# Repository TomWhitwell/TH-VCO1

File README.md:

# TH-VCO1

This is a Eurorack Layout for the [Thomas Henry VCO 1](http://www.birthofasynth.com/Thomas_Henry/Pages/VCO-1.html) Oscillator. 

**NB: All rights to this design rest with Thomas Henry. I do not claim or grant any copyright or license to this design. I am not selling any boards. I have not been able to contact Thomas, and will take this page down if he asks me to.** 

I made very minor changes from Thomas' original to make it work on 12v - detailed here: https://muffwiggler.com/forum/viewtopic.php?t=49671

This layout is for a modern LM13700 OTA replacing the old 3080, with a That 340 chip providing the matched transistor pairs. The only other non-standard components are a [2K 3300ppm Tempco](https://www.thonk.co.uk/shop/tempco-resistor-anakeohm-1-3300ppm-x3/) as R2, and a Polystyrene 1nf cap as C3.  

It all works very well, fantastic FM, nice looking and sounding sines. I was able to trim it to 4-5 octaves before getting bored. I haven't used multi-turn trimmers, so it might be harder to trim more accurately. On my second build I haven't trimmed anything, and it works beautifully for my needs. 

Quick demo here: https://www.instagram.com/p/_etQT6DmdM/

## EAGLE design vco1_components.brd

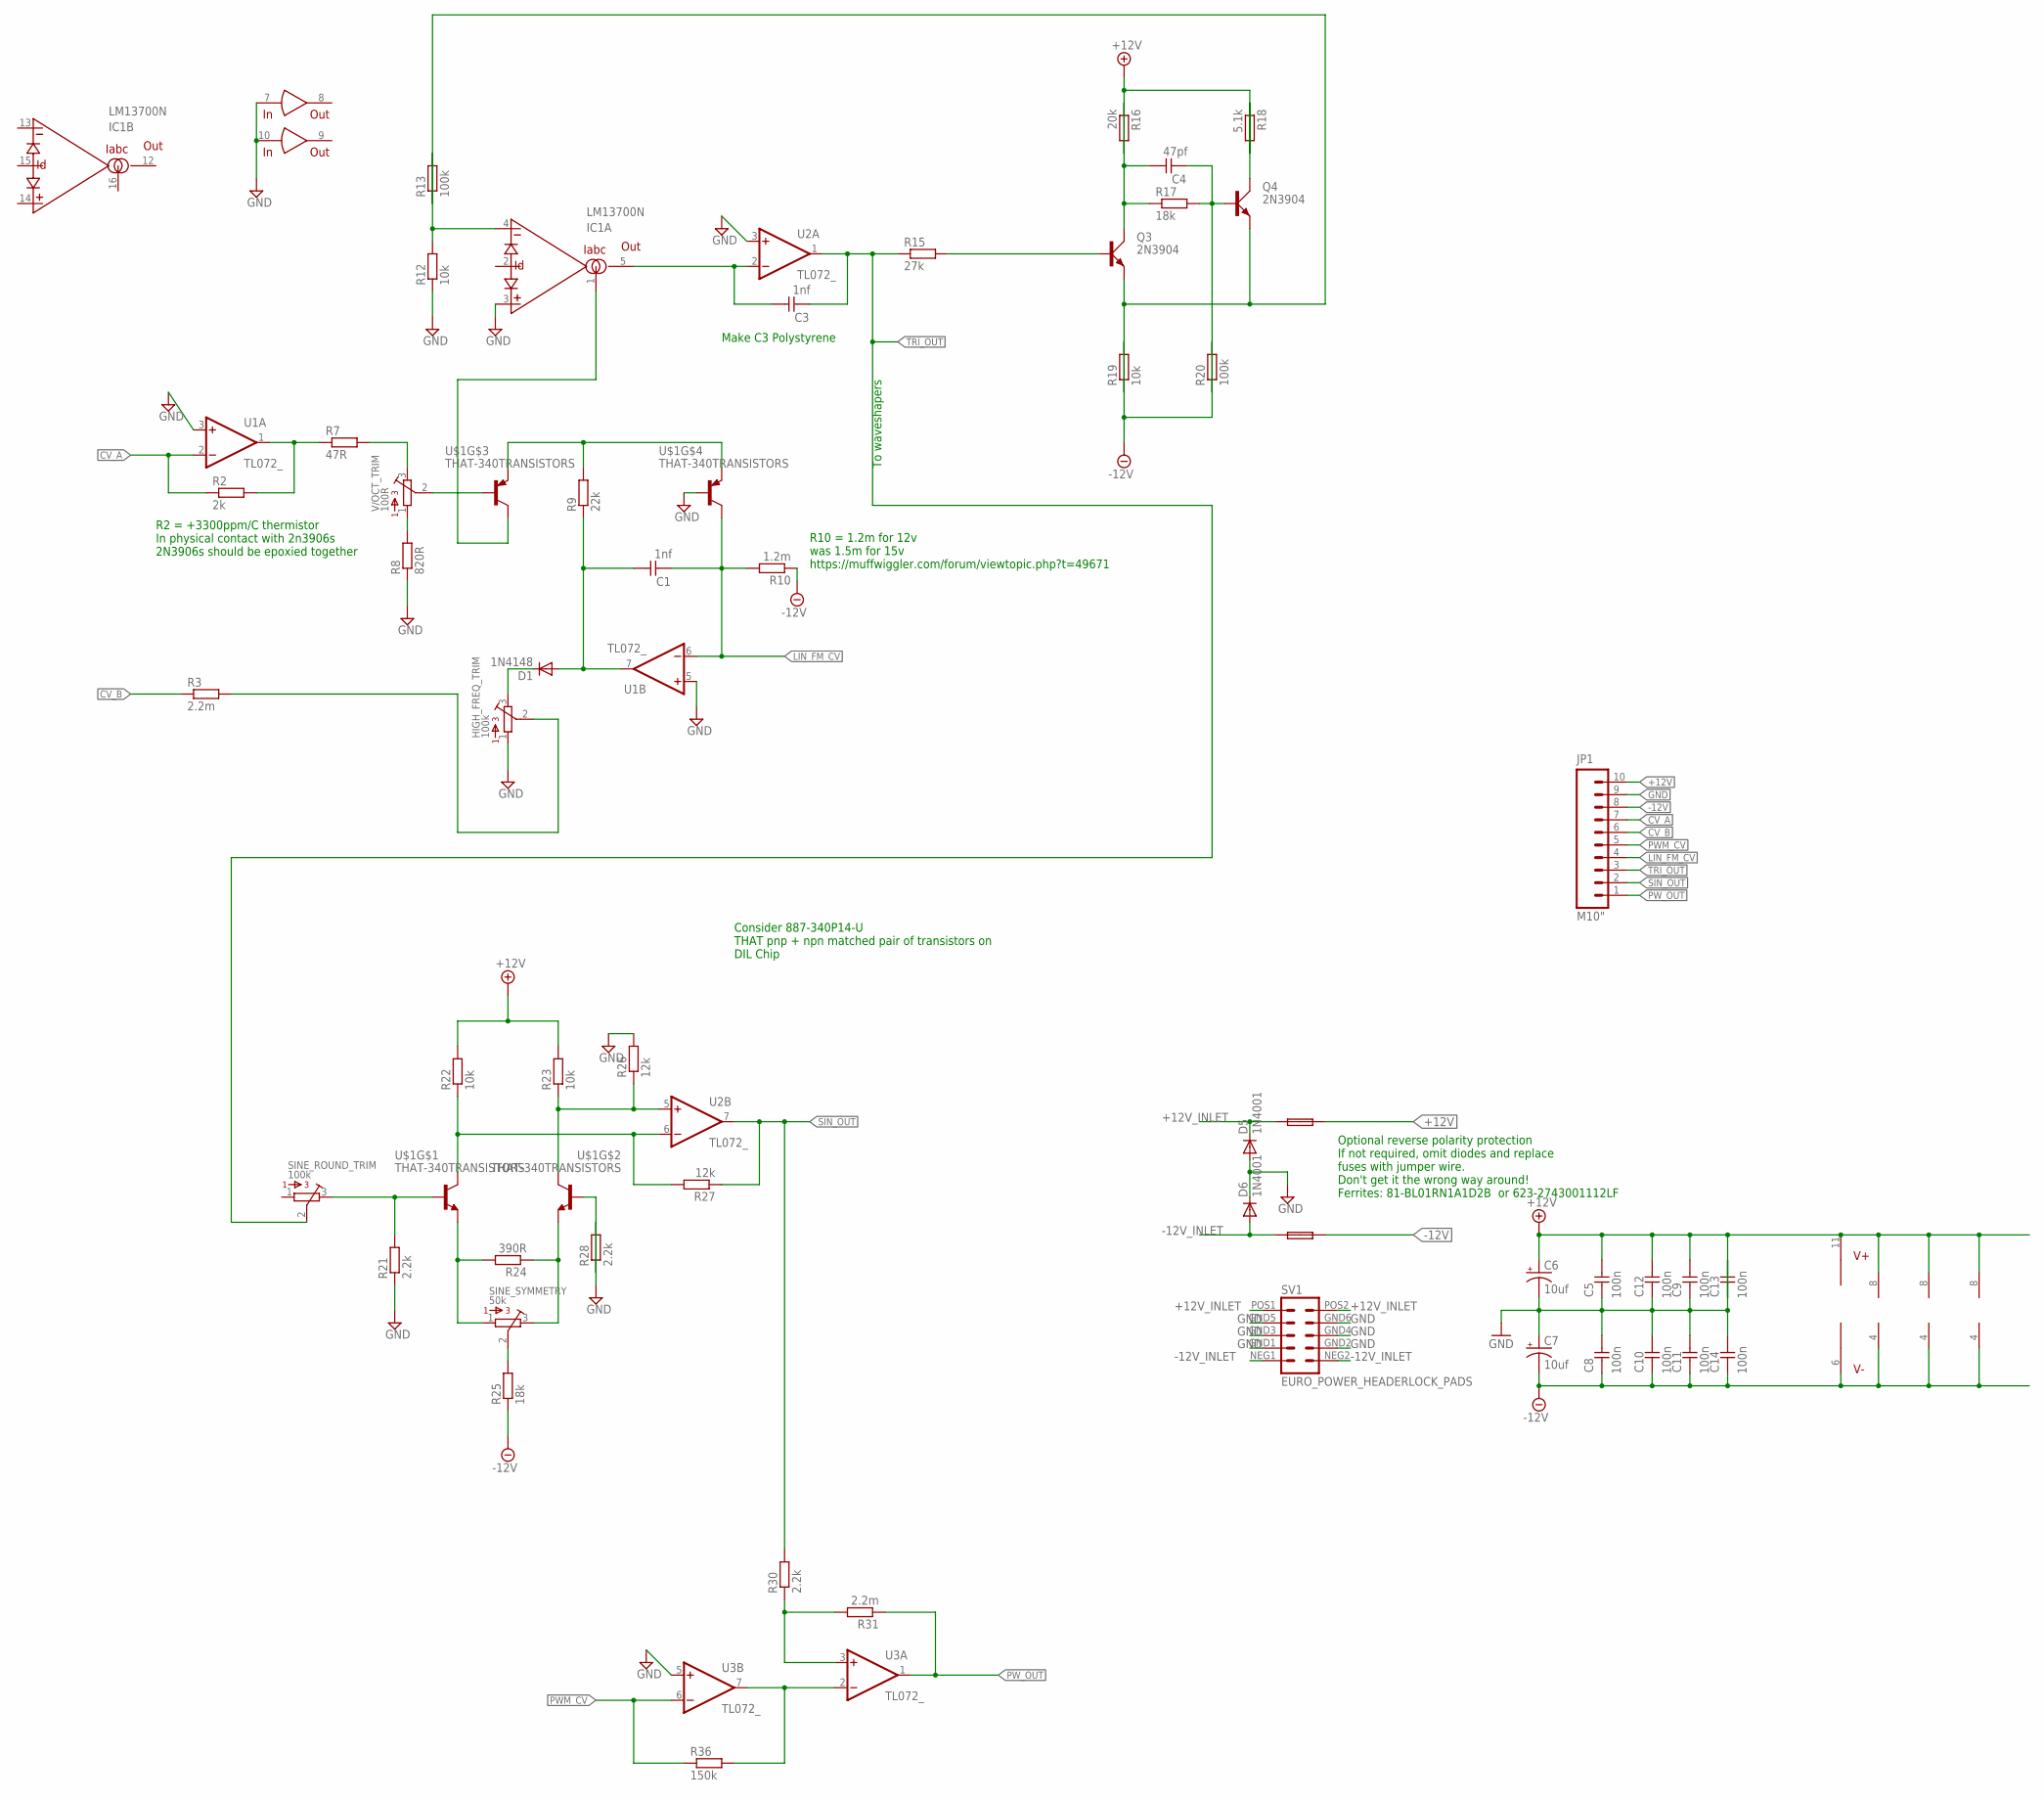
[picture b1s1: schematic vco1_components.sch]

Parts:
C1, C3: 1nf; C050-024X044
C4: 47pf; C050-024X044
C5, C8, C9, C10, C11, C12, C13, C14: 100n; C050-024X044
C6, C7: 10uf; CPOL-RADIAL-10UF-25V
D1: 1N4148; DO35-7
D5, D6: 1N4001; DO41-10
F1, F2: FUSE; C050H075X075
HIGH_FREQ_TRIM: 100k; BOURNS_3362P_TRIMMER
IC1: LM13700N; DIL16
JP1: M10"; 1X10
Q3, Q4: 2N3904; TO92D
R2: 2k; 7MM_RESISTOR
R3, R31: 2.2m; 7MM_RESISTOR
R7: 47R; 7MM_RESISTOR
R8: 820R; 7MM_RESISTOR
R9: 22k; 7MM_RESISTOR
R10: 1.2m; 7MM_RESISTOR
R12, R19, R22, R23: 10k; 7MM_RESISTOR
R13, R20: 100k; 7MM_RESISTOR
R15: 27k; 7MM_RESISTOR
R16: 20k; 7MM_RESISTOR
R17, R25: 18k; 7MM_RESISTOR
R18: 5.1k; 7MM_RESISTOR
R21, R28, R30: 2.2k; 7MM_RESISTOR
R24: 390R; 7MM_RESISTOR
R26, R27: 12k; 7MM_RESISTOR
R36: 150k; 7MM_RESISTOR
SINE_ROUND_TRIM: 100k; BOURNS_3362P_TRIMMER
SINE_SYMMETRY: 50k; BOURNS_3362P_TRIMMER
SV1: EURO_POWER_HEADERLOCK_PADS; EURO_PWR_HEADER_LOCK
U1, U2, U3: TL072_; DIL08
U$1: THAT-340TRANSISTORS; THAT340
V/OCT_TRIM: 100R; BOURNS_3362P_TRIMMER

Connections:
+12V: C5.1, C6.1 (+), C9.1, C12.1, C13.2, F1.2, IC1.11 (V+), JP1.10, R16.2, R18.2, R22.2, R23.2, U1.8 (V+), U2.8 (V+), U3.8 (V+)
+12V_INLET: D5.C, F1.1, SV1.POS1 (10), SV1.POS2 (9)
-12V: C7.2 (-), C8.2, C10.2, C11.2, C14.2, F2.2, IC1.6 (V-), JP1.8, R10.1, R19.2, R20.2, R25.1, U1.4 (V-), U2.4 (V-), U3.4 (V-)
-12V_INLET: D6.A, F2.1, SV1.NEG1 (2), SV1.NEG2 (1)
CV_A: JP1.7, R2.1, U1.2 (-IN)
CV_B: JP1.6, R3.1
GND: C5.2, C6.2 (-), C7.1 (+), C8.1, C9.2, C10.1, C11.1, C12.2, C13.1, C14.1, D5.A, D6.C, HIGH_FREQ_TRIM.1, IC1.3 (+IN), IC1.7 (IN), IC1.10 (IN), JP1.9, R8.1, R12.1, R21.1, R26.2, R28.2, SV1.GND1 (4), SV1.GND2 (3), SV1.GND3 (6), SV1.GND4 (5), SV1.GND5 (8), SV1.GND6 (7), U1.3 (+IN), U1.5 (+IN), U2.3 (+IN), U3.5 (+IN), U$1.9 (B)
LIN_FM_CV: C1.2, JP1.4, R10.2, U1.6 (-IN), U$1.8 (C)
unnamed: R2.2, R7.1, U1.1 (OUT)
unnamed: R7.2, V/OCT_TRIM.3
unnamed: R8.2, V/OCT_TRIM.1
unnamed: U$1.6 (B), V/OCT_TRIM.2
unnamed: R9.2, U$1.5 (E), U$1.10 (E)
unnamed: IC1.1 (IABC), U$1.7 (C)
unnamed: C1.1, D1.A, R9.1, U1.7 (OUT)
unnamed: D1.C, HIGH_FREQ_TRIM.3
unnamed: HIGH_FREQ_TRIM.2, R3.2
unnamed: IC1.4 (-IN), R12.2, R13.2
unnamed: C3.1, IC1.5 (OUT), U2.2 (-IN)
unnamed: Q3.B, R15.2
unnamed: C4.1, Q3.C, R16.1, R17.1
unnamed: R21.2, SINE_ROUND_TRIM.3, U$1.2 (B)
unnamed: C4.2, Q4.B, R17.2, R20.1
unnamed: Q4.C, R18.1
unnamed: R25.2, SINE_SYMMETRY.2
unnamed: Q3.E, Q4.E, R13.1, R19.1
unnamed: R22.1, R27.2, U2.6 (-IN), U$1.1 (C)
unnamed: R23.1, R26.1, U2.5 (+IN), U$1.14 (C)
unnamed: R24.2, SINE_SYMMETRY.1, U$1.3 (E)
unnamed: R24.1, SINE_SYMMETRY.3, U$1.12 (E)
unnamed: R28.1, U$1.13 (B)
unnamed: R30.1, R31.2, U3.3 (+IN)
unnamed: R36.2, U3.2 (-IN), U3.7 (OUT)
PWM_CV: JP1.5, R36.1, U3.6 (-IN)
PW_OUT: JP1.1, R31.1, U3.1 (OUT)
SIN_OUT: JP1.2, R27.1, R30.2, U2.7 (OUT)
TRI_OUT: C3.2, JP1.3, R15.1, SINE_ROUND_TRIM.2, U2.1 (OUT)

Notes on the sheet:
To waveshapers
R2 = +3300ppm/C thermistor In physical contact with 2n3906s 2N3906s should be epoxied together
Make C3 Polystyrene
R10 = 1.2m for 12v was 1.5m for 15v https://muffwiggler.com/forum/viewtopic.php?t=49671
Consider 887-340P14-U THAT pnp + npn matched pair of transistors on DIL Chip
Optional reverse polarity protection If not required, omit diodes and replace fuses with jumper wire. Don't get it the wrong way around! Ferrites: 81-BL01RN1A1D2B or 623-2743001112LF

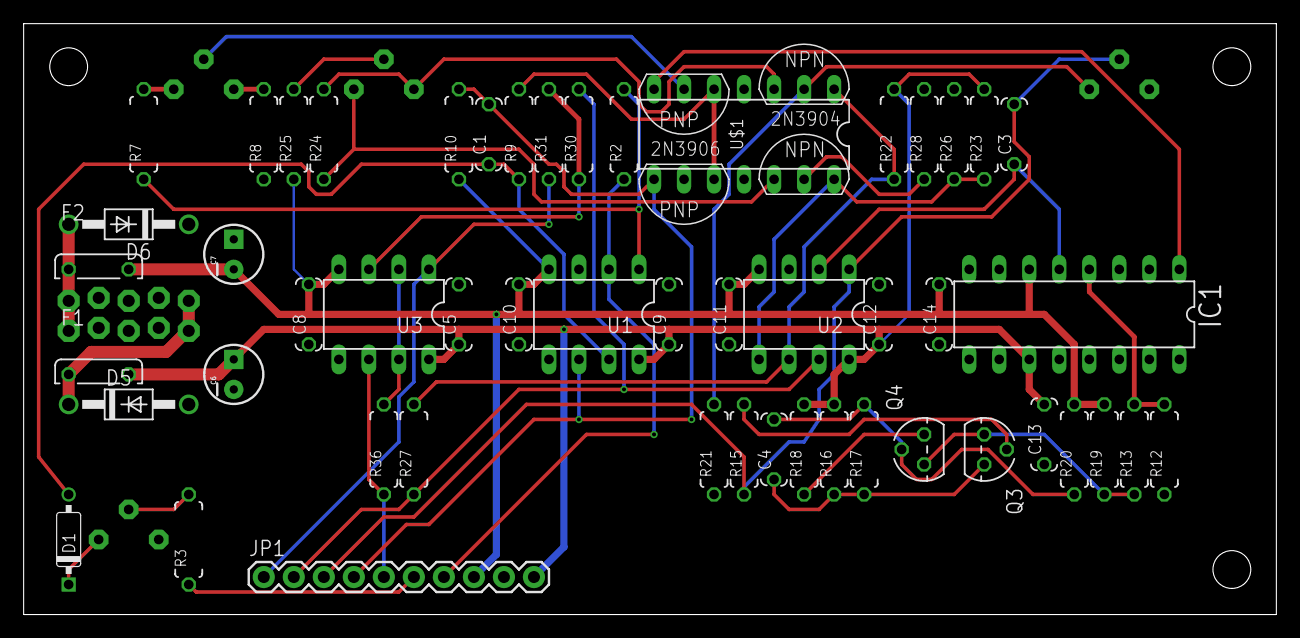
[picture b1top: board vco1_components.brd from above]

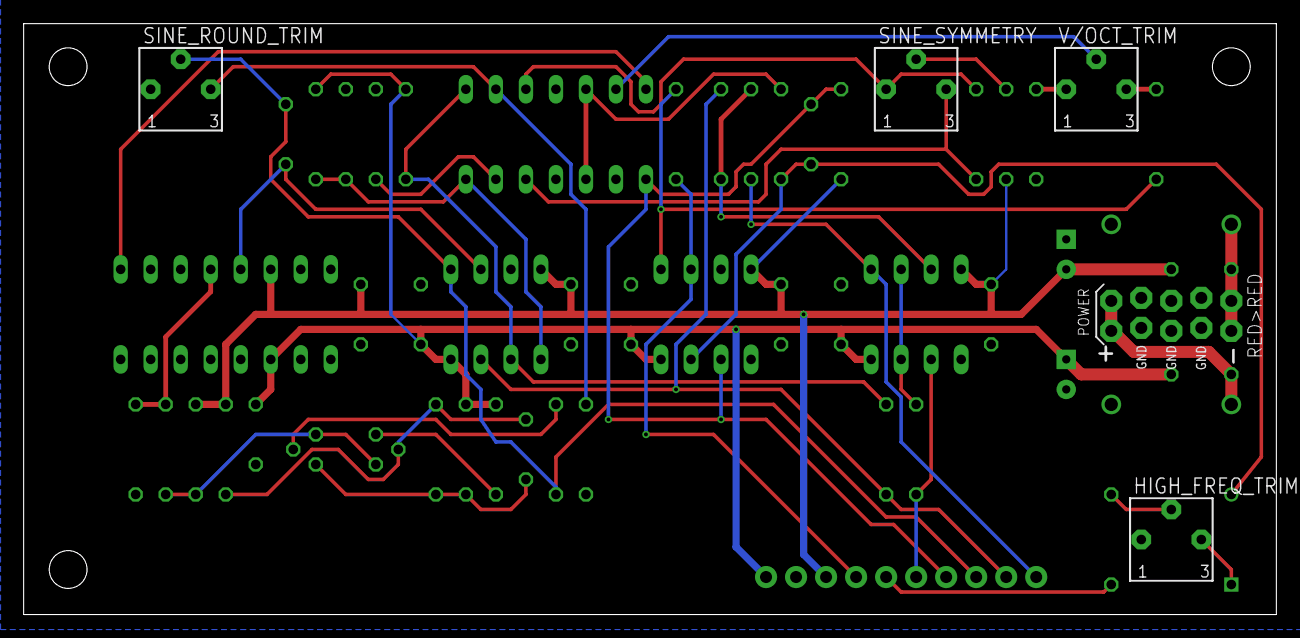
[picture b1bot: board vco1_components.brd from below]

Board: 4 copper layers, 106.0 x 50.0 mm, 59 parts (5 on the bottom side), 37 nets.

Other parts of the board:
U$2, U$3, U$4: MOUNTING_HOLE

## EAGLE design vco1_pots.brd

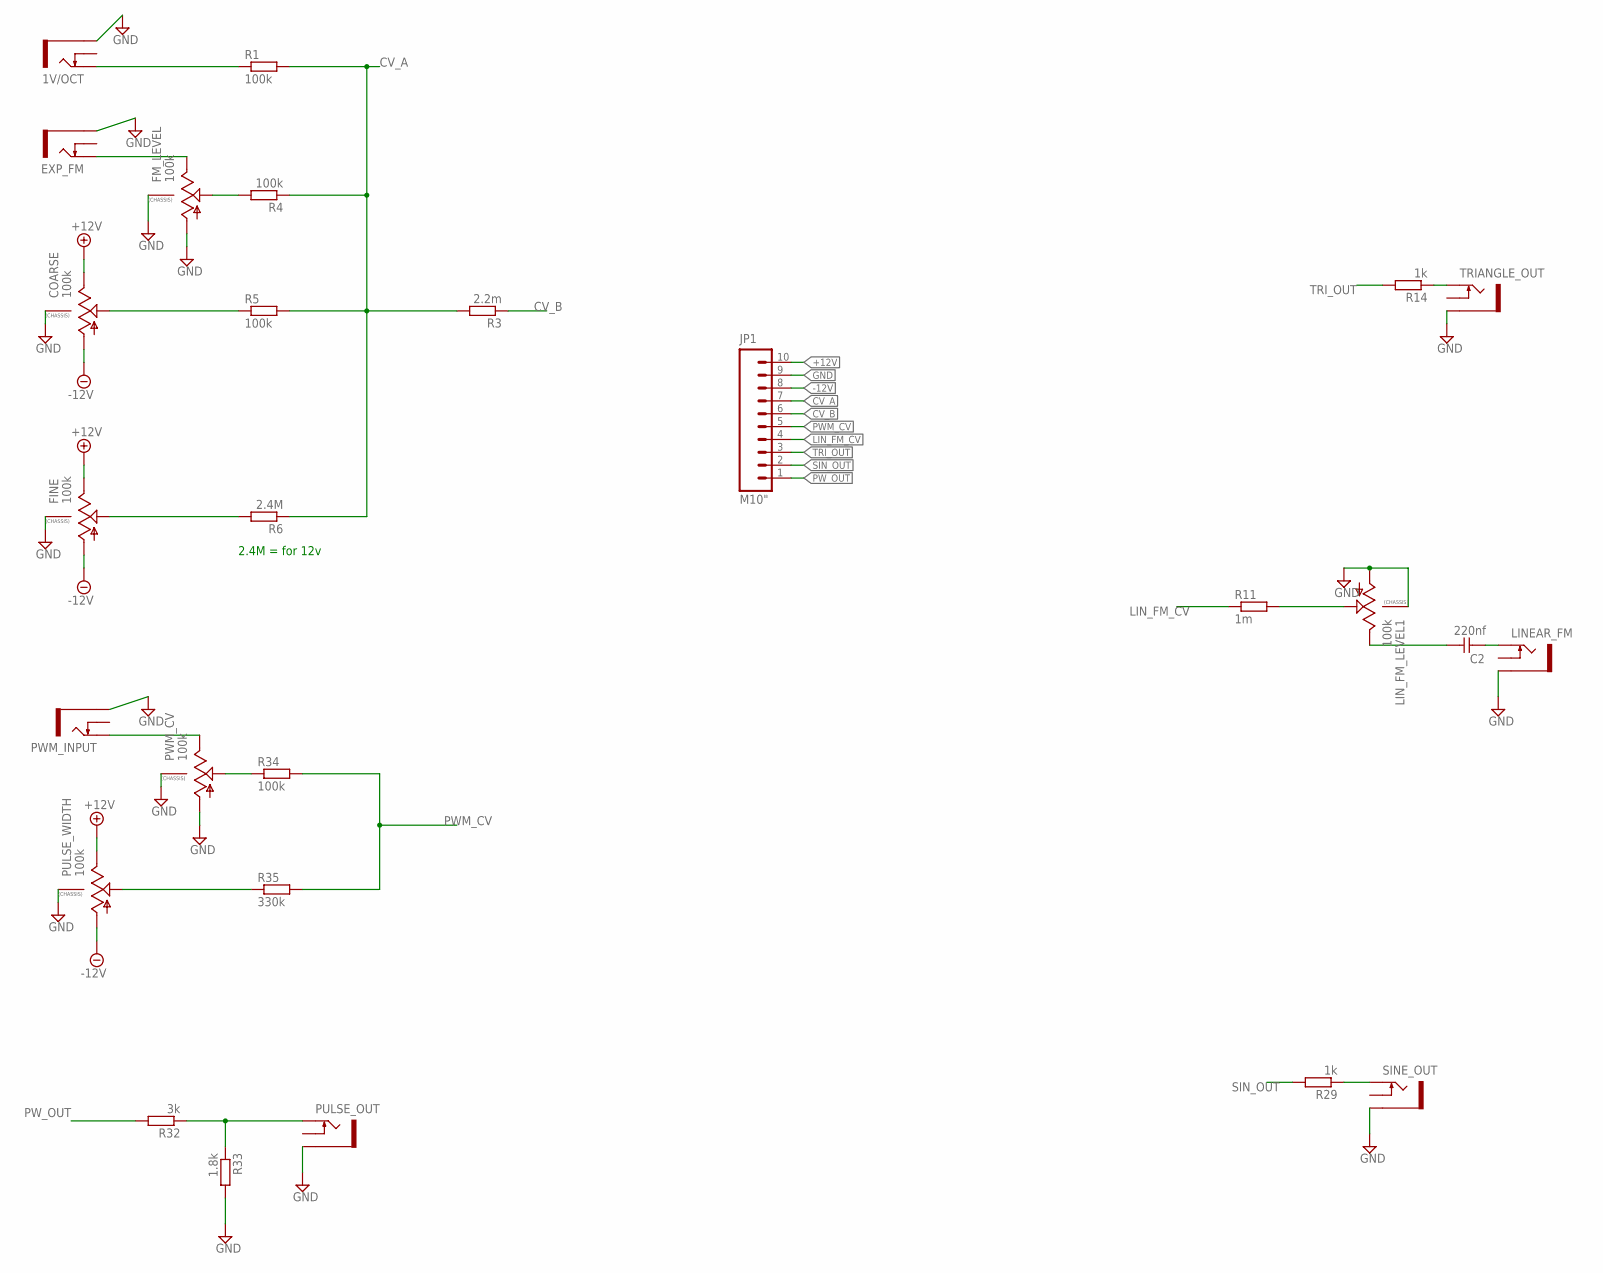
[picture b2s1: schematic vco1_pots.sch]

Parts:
1V/OCT: THONKICONNNEW; WQP-PJ301M-12_JACK
C2: 220nf; C050-024X044
COARSE: 100k; 9MM_SNAP-IN_POT
EXP_FM: THONKICONNNEW; WQP-PJ301M-12_JACK
FINE: 100k; 9MM_SNAP-IN_POT
FM_LEVEL: 100k; 9MM_SNAP-IN_POT
JP1: M10"; 1X10
LINEAR_FM: THONKICONNNEW; WQP-PJ301M-12_JACK
LIN_FM_LEVEL1: 100k; 9MM_SNAP-IN_POT
PULSE_OUT: THONKICONNNEW; WQP-PJ301M-12_JACK
PULSE_WIDTH: 100k; 9MM_SNAP-IN_POT
PWM_CV: 100k; 9MM_SNAP-IN_POT
PWM_INPUT: THONKICONNNEW; WQP-PJ301M-12_JACK
R1, R4, R5, R34: 100k; 7MM_RESISTOR
R3: 2.2m; 7MM_RESISTOR
R6: 2.4M; 7MM_RESISTOR
R11: 1m; 7MM_RESISTOR
R14, R29: 1k; 7MM_RESISTOR
R32: 3k; 7MM_RESISTOR
R33: 1.8k; 7MM_RESISTOR
R35: 330k; 7MM_RESISTOR
SINE_OUT: THONKICONNNEW; WQP-PJ301M-12_JACK
TRIANGLE_OUT: THONKICONNNEW; WQP-PJ301M-12_JACK

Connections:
+12V: COARSE.3 (E), FINE.3 (E), JP1.10, PULSE_WIDTH.3 (E)
-12V: COARSE.1 (A), FINE.1 (A), JP1.8, PULSE_WIDTH.1 (A)
CV_A: JP1.7, R1.2, R3.2, R4.1, R5.2, R6.1
CV_B: JP1.6, R3.1
GND: 1V/OCT.P$3_SLEEVE (SLEEVE), COARSE.CHASSIS2, EXP_FM.P$3_SLEEVE (SLEEVE), FINE.CHASSIS2, FM_LEVEL.1 (A), FM_LEVEL.CHASSIS2, JP1.9, LINEAR_FM.P$3_SLEEVE (SLEEVE), LIN_FM_LEVEL1.1 (A), LIN_FM_LEVEL1.CHASSIS2, PULSE_OUT.P$3_SLEEVE (SLEEVE), PULSE_WIDTH.CHASSIS2, PWM_CV.1 (A), PWM_CV.CHASSIS2, PWM_INPUT.P$3_SLEEVE (SLEEVE), R33.2, SINE_OUT.P$3_SLEEVE (SLEEVE), TRIANGLE_OUT.P$3_SLEEVE (SLEEVE)
LIN_FM_CV: JP1.4, R11.1
unnamed: 1V/OCT.P$1_TIP (TIP), R1.1
unnamed: EXP_FM.P$1_TIP (TIP), FM_LEVEL.3 (E)
unnamed: FM_LEVEL.2 (S), R4.2
unnamed: COARSE.2 (S), R5.1
unnamed: FINE.2 (S), R6.2
unnamed: LIN_FM_LEVEL1.2 (S), R11.2
unnamed: R14.1, TRIANGLE_OUT.P$1_TIP (TIP)
unnamed: C2.1, LIN_FM_LEVEL1.3 (E)
unnamed: C2.2, LINEAR_FM.P$1_TIP (TIP)
unnamed: R29.1, SINE_OUT.P$1_TIP (TIP)
unnamed: PULSE_OUT.P$1_TIP (TIP), R32.1, R33.1
unnamed: PWM_CV.3 (E), PWM_INPUT.P$1_TIP (TIP)
unnamed: PWM_CV.2 (S), R34.1
unnamed: PULSE_WIDTH.2 (S), R35.1
PWM_CV: JP1.5, R34.2, R35.2
PW_OUT: JP1.1, R32.2
SIN_OUT: JP1.2, R29.2
TRI_OUT: JP1.3, R14.2

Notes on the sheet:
2.4M = for 12v

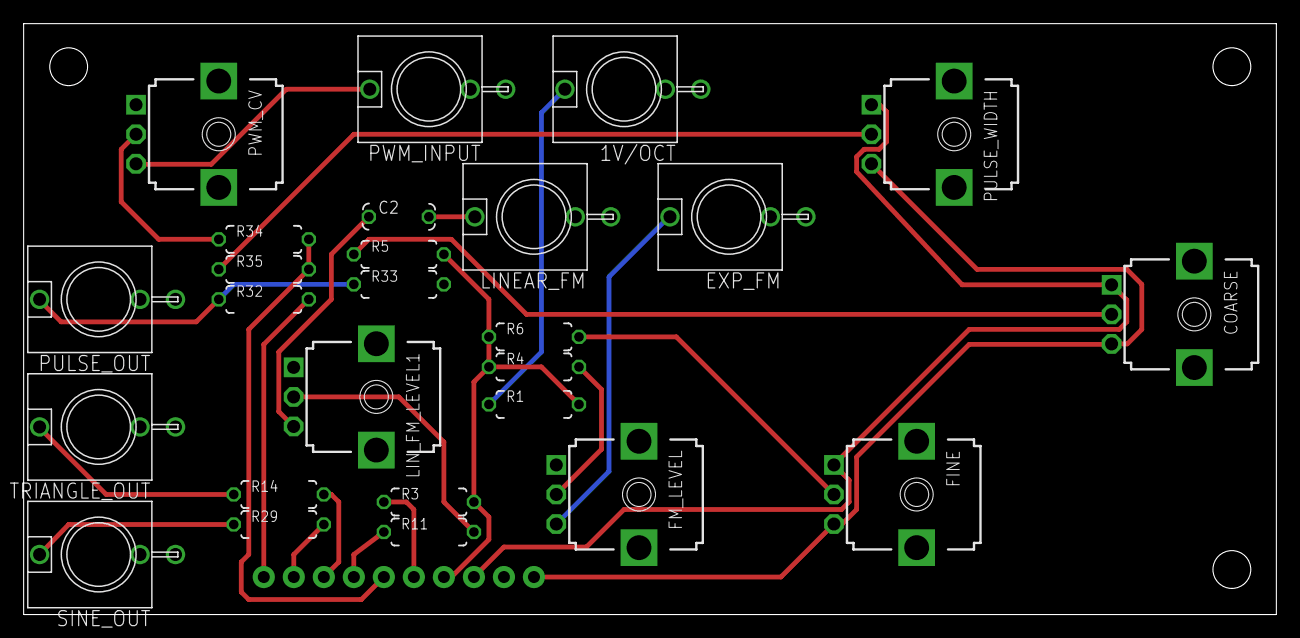
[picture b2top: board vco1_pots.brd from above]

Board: 4 copper layers, 106.0 x 50.0 mm, 30 parts (1 on the bottom side), 24 nets.

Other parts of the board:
U$1, U$2, U$3: MOUNTING_HOLE

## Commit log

2016-01-02 Upload files
2016-01-04 2n3906 3094 diagram
2016-01-04 Transistor outlines on THAT 340

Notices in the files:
parts and their libraries:
SparkFun-Passives: Licensing: CC v3.0 Share-Alike You are welcome to use this library for commercial purposes.
